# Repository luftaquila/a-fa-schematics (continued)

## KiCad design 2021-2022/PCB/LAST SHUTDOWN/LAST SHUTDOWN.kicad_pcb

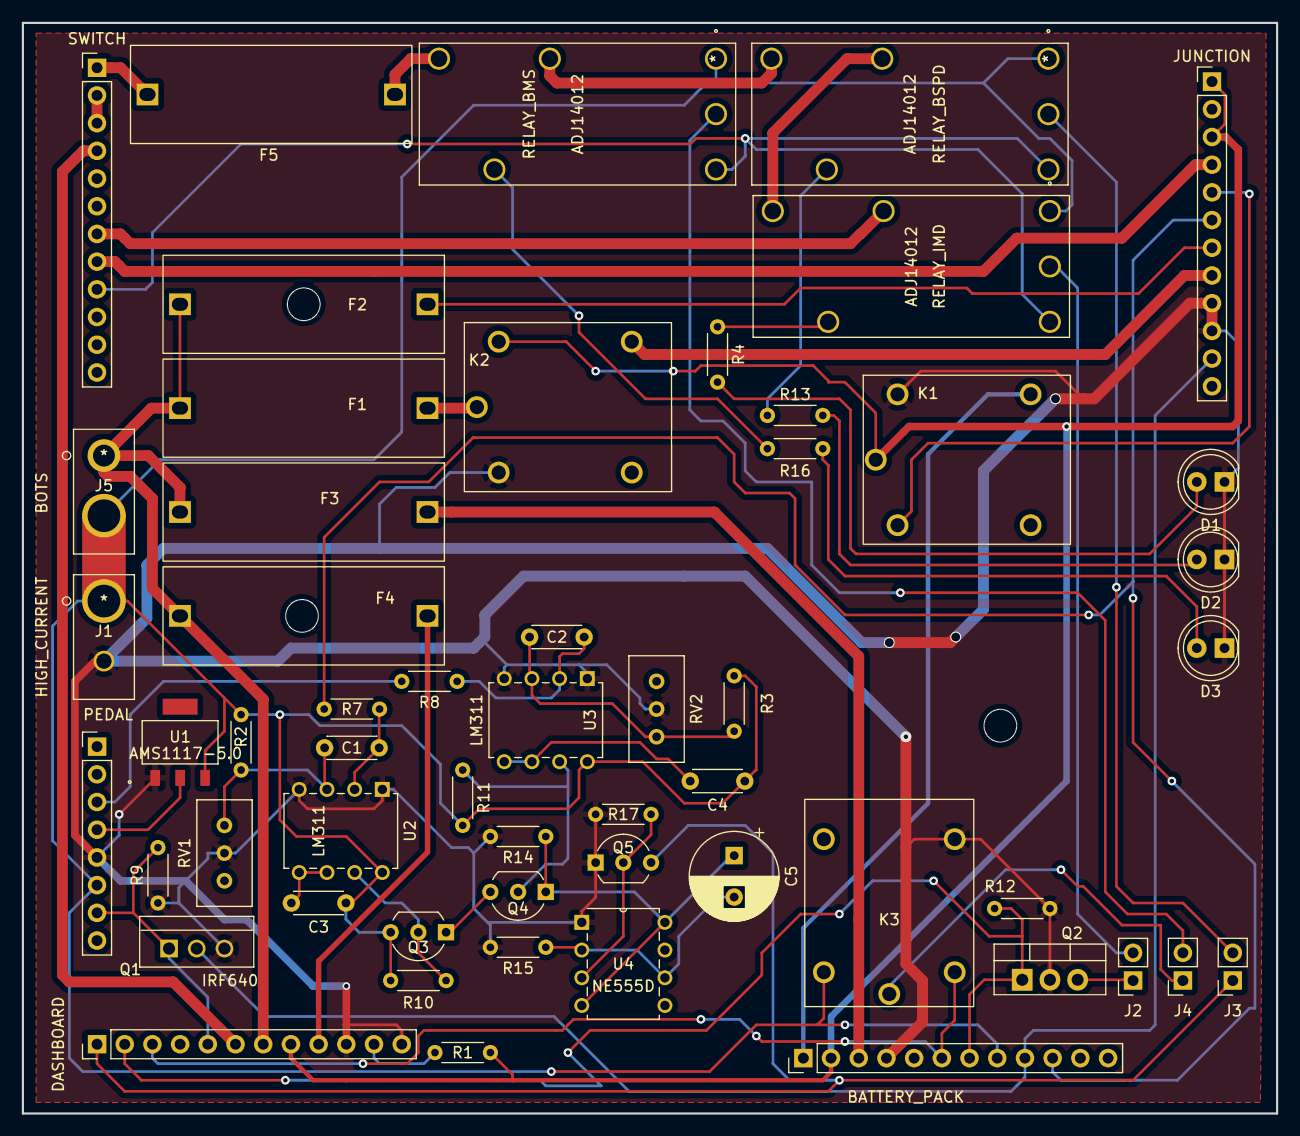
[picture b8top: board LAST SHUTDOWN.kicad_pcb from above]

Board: 2 copper layers, 115.0 x 100.0 mm, 55 parts (0 on the bottom side), 52 nets.

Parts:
BATTERY_PACK: Conn_01x12_Male; PinHeader_1x12_P2.54mm_Vertical
C1, C2, C3, C4: 1nF; C_Disc_D4.3mm_W1.9mm_P5.00mm
C5: 10uF; CP_Radial_D8.0mm_P3.80mm
D1, D2, D3: LED; LED_D5.0mm
DASHBOARD: Conn_01x12_Male; PinHeader_1x12_P2.54mm_Vertical
F1, F3, F5: 4A Fuse; 646SERIES_FUSEHOLDER
F2: 1A Fuse; 646SERIES_FUSEHOLDER
F4: 2A Fuse; 646SERIES_FUSEHOLDER
J1: HIGH_CURRENT; 0039281023 5566-02A
J2, J3, J4: Conn_01x02_Male; PinSocket_1x02_P2.54mm_Vertical
J5: BOTS; 0039281023 5566-02A
JUNCTION: Conn_01x12_Male; PinHeader_1x12_P2.54mm_Vertical
K1, K2, K3: HR702NH-DC12V
PEDAL: Conn_01x08_Male; PinHeader_1x08_P2.54mm_Vertical
Q1: IRF640; IRF640NPBF
Q2: IRF9540N; TO-220-3_Vertical
Q3, Q4, Q5: 2N3904; TO-92_Inline_Wide
R1, R4, R9, R10, R11, R12, R13, R16: 10k; R_Axial_DIN0204_L3.6mm_D1.6mm_P5.08mm_Horizontal
R2, R3, R14: 4.7k; R_Axial_DIN0204_L3.6mm_D1.6mm_P5.08mm_Horizontal
R7, R8, R17: 1k; R_Axial_DIN0204_L3.6mm_D1.6mm_P5.08mm_Horizontal
R15: 62k; R_Axial_DIN0204_L3.6mm_D1.6mm_P5.08mm_Horizontal
RELAY_BMS: ADJ14012
RELAY_BSPD: ADJ14012
RELAY_IMD: ADJ14012
RV1, RV2: R_Potentiometer_US; Potentiometer_Bourns_3296W_Vertical
SWITCH: Conn_01x12_Male; PinHeader_1x12_P2.54mm_Vertical
U1: AMS1117-5.0
U2, U3: LM311; LM311P
U4: NE555D; NE555P

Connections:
AIR+_ACTIVE: BATTERY_PACK.1, K1.14
AIR+_ACTIVE_SIG: JUNCTION.5, K1.6
AIR-_ACTIVE: BATTERY_PACK.2, DASHBOARD.8, JUNCTION.1, JUNCTION.3, K1.7, K2.2, R1.1
BMS_FAULT: BATTERY_PACK.6, DASHBOARD.3, K3.6
BMS_HALL: BATTERY_PACK.10, JUNCTION.6, R7.2
BOTS_IN: BATTERY_PACK.8, C3.1, C4.1, J1.1, J5.2, K3.2, PEDAL.6, Q3.3 (C), R2.2, R3.2, R10.1, R11.2, RELAY_BMS.1 (V), RELAY_BSPD.1 (V), RELAY_IMD.1 (V), U1.3 (VI), U2.8 (V+), U3.8 (V+)
BOTS_OUT: DASHBOARD.7, F1.2, F2.2, F3.2, F4.2, J5.1
BRAKE: PEDAL.3, R8.2
BRAKE_GND: BATTERY_PACK.4, D1.1 (K), D2.1 (K), D3.1 (K), DASHBOARD.10, DASHBOARD.12, J1.2, JUNCTION.9, JUNCTION.10, K1.2, K2.6, K3.1, PEDAL.5, Q1.3 (S), Q2.2 (D), Q5.1 (E), R9.1, R12.1, R14.2, R15.2, R17.2, RV1.2, RV2.2, U1.1 (GND), U2.1 (GND), U2.4 (V-), U3.1 (GND), U3.4 (V-), U4.1 (GND)
BRAKE_LIGHT-: BATTERY_PACK.9, JUNCTION.11, Q1.2 (D)
BRAKE_OUT: DASHBOARD.5, PEDAL.7, Q1.1 (G), R9.2
BRAKE_PWR: PEDAL.4, U1.2 (VO)
BSPD_FAULT: DASHBOARD.1, J3.1, Q5.3 (C)
HVD_INTERLOCK_OUT: JUNCTION.4, SWITCH.8
HV_ACTIVE_LED: DASHBOARD.11, R1.2
HV_AUX1_OUT: DASHBOARD.6, SWITCH.4
HV_AUX2_OUT: SWITCH.2, SWITCH.3
HV_AUX3_OUT: F5.1, SWITCH.1
HV_MASTER_OUT: RELAY_IMD.2 (Out), SWITCH.7
IMD_FAULT: BATTERY_PACK.7, DASHBOARD.2, Q2.1 (G), R12.2
LV_ECU: DASHBOARD.9, F4.1
LV_INV: JUNCTION.8, K2.14
LV_PACK: BATTERY_PACK.3, F3.1
LV_TSAL: F2.1, JUNCTION.7
unnamed: C1.1, R7.1, U2.2 (+)
unnamed: C1.2, R2.1, RV1.1, U2.3 (-)
unnamed: C2.1, R8.1, U3.2 (+)
unnamed: C2.2, R3.1, RV2.1, U3.3 (-)
unnamed: C3.2, U2.5 (BAL), U2.6 (STRB)
unnamed: C4.2, U3.5 (BAL), U3.6 (STRB)
unnamed: C5.1, Q4.1 (E), R14.1, U4.4 (R), U4.8 (VCC)
unnamed: C5.2, R15.1, U4.2 (TR), U4.6 (THR)
unnamed: D1.2 (A), R4.2
unnamed: D2.2 (A), R13.2
unnamed: D3.2 (A), R16.2
unnamed: F1.1, K2.7
unnamed: F5.2, RELAY_BMS.4 (12V)
unnamed: J2.1, Q2.3 (S)
unnamed: J2.2, RELAY_IMD.9 (D)
unnamed: J3.2, RELAY_BSPD.9 (D)
unnamed: J4.1, K3.7
unnamed: J4.2, RELAY_BMS.9 (D)
unnamed: Q3.1 (E), Q4.3 (C)
unnamed: Q3.2 (B), R10.2, U2.7
unnamed: Q4.2 (B), R11.1, U3.7
unnamed: Q5.2 (B), R17.1, U4.3 (Q)
unnamed: R4.1, RELAY_IMD.6 (N)
unnamed: R13.1, RELAY_BSPD.6 (N)
unnamed: R16.1, RELAY_BMS.6 (N)
unnamed: RELAY_BMS.2 (Out), RELAY_BSPD.4 (12V)
unnamed: RELAY_BSPD.2 (Out), RELAY_IMD.4 (12V)
SHUTDOWN_RESET: RELAY_BMS.8 (L), RELAY_BSPD.8 (L), RELAY_IMD.8 (L), SWITCH.9

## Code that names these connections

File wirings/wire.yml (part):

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
  LV PCB 1-A:
    <<: *LPT
    pinlabels: [LV_PACK+, LV_PACK-, -, AIR+, AIR-, -, BMS_FAULT, IMD_FAULT, -, ON_COOLING, ON_PUMP, ON_RAD_FAN, ON_BATT_FAN, -, CAN_H_BMS, CAN_L_BMS]

  LV PCB 1-B:
    <<: *LPT
    pinlabels: [FORWARD_ENABLE, BRAKE_SW_INV, REGEN_DISABLE, \PROG_ENA, -, CAN_H_INV, CAN_L_INV, RS232_TX, RS232_RX, -, GND_INV, -, AIR_DRIVE, LV_INV+, LV_INV-, IGNITION]

  LV PCB 1-C:
    <<: *LPT
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
  LV PCB 1-F:
    <<: *LPT
    pinlabels: [LV_JNC+, LV_JNC-, HALL_SIG, HVD1, HVD2, -, BRAKE_LIGHT+, BRAKE_LIGHT-, BRAKE_PWR, BRAKE_SIG, BRAKE_GND, BRAKE_SW1, BRAKE_SW2, BOTS1, -, -, BOTS2, LV_BATT+, LV_BATT-]

  LV PCB 1-G:
    <<: *LPT
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
  HV BATT 3-A:
    <<: *LPT
    pinlabels: [LV_PACK+, LV_PACK-, AIR+, AIR-, BMS_FAULT, IMD_FAULT, -, ON_COOLING, ON_PUMP, ON_RAD_FAN, ON_BATT_FAN, CAN_H_BMS, CAN_L_BMS, PRECHARGE_DRIVE, -, CHARGE_POWER, CHARGER_SAFETY, CHARGER_INTERLOCK1, CHARGER_INTERLOCK2]

  HV BATT 3-B:
    <<: *LPT
    pinlabels: [LV_TSAL+, LV_PUMP+, LV_PUMP-, -, LV_FAN_L+, LV_FAN_L-, LV_FAN_R+, -, LV_FAN_R-, -, TSAL_GREEN, TSAL_RED]


  ######################## INVERTER ########################
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
  JUNCTION 5-B:
    <<: *LPT
    pinlabels: [LV_JNC+, LV_JNC-, -, HALL_SIG, -, HVD1, HVD2, -, -, -, -, -, -, -, -, -, -, LV_BATT+, LV_BATT-]


  ####################### DASHBOARD ########################
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
  CHARGE SHUTDOWN A:
    <<: *LPT
    pinlabels: [-, -, AIR-, -, -, -, -, CHARGE_POWER, LV_PACK-, LV_PACK+, CHARGER_INTERLOCK1, CHARGER_INTERLOCK2, CHARGER_SAFETY, AIR+, -, -, -, IMD_FAULT, -]

  CHARGE SHUTDOWN B:
    <<: *RS232
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
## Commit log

2023-03-01 update schematics snapshot
2023-07-19 update: schematics and wirings to current state
2023-08-12 refactor: 23/08/13 new LV PCB
2023-08-12 update: 23/08/13 current wiring system
2023-08-14 update: 23/08/14
2023-08-14 fix: broken LV_PCB link
